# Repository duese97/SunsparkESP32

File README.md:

# SunsparkESP32
A new ESP32 hardware platform for low power applications.

This PCB utilizes a small solar cell in order to harvest energy and store it in a supercapacitor.

*The rendered PCB for the SunsparkESP32*

## Features
1. ESP32 S2 Mini module with a single core MCU: Most projects utilize one core anyway or don't benefit much form a second one. So no current is wasted by idling unnecessary.
2. Native USB support: Converter for RS232 can be connected externally. Many USB to RS232 transceivers have a high quiescent consumption. They are mostly needed for debugging, in order to show data to a console. Flashing the chip also works via the USB bootloader (and is also faster).
3. Integrated open drain MOSFET: Control high power external peripherals and turn them off when not needed.
4. VBUS from USB utilized automatically as backup supply, so debugging does not drain the supercap.
5. Optional RF95/96/97/98 LoRa module can be added (library used: https://github.com/sandeepmistry/arduino-LoRa/tree/master)

## Application example
I included some FW which realizes a simple WiFI weather station with a common BME280. However it can be easily altered to work with different or more sensors as well. It works well enough that it can sustain it's 10min scheduled data delivery indoors, in my living room.

Shutting down/entering deepsleep immediately after sending the UDP packet seems not to work (underlying RTOS or network stack takes some time). Thus I additionally set up the the UDP Server in a way that it sends a small sting back, upon receiving data.
The provided code does not utilizes this any further, but it could be a nice way for a two way communication. The ESP32 will run 1s at most, an then enter sleep again:

*Example flow for parsing incoming results in Node RED*

There is also some small logic, which handles a depletion (or charging) of the supercap by altering the deepsleep period.

I found it helpful to include a runtime checked "debug mode". Tieing a GPIO to high, and to "artificially" shorten the sleep time, so I can debug more easily. Setting it to low put it back into "normal" mode and also disabled some UART prints.

Note: Altered Adafruit_BME280::begin so that is does NOT call
Adafruit_BME280::init upon each wakeup of device -> sensor is permanently
supplied with VCC and does not need a lengthy re-init each time

## Requirements for external components/assembly
1. The open circuit voltage of the solar cell should not exceed 3.3V. Recommended is 1.5V @ 0.65W
2. Make sure to protect the PCB when using it outdoors. Especially the Mega Ohm resistors are sensitive to water. I use clear nail polish for this. 
*The PCB with the solar cell and a BME280 soldered to it. The 433MHz antenna for the RF96 is also visible.*
3. Mechanically a 3D printed assembly can accommodate the circuit shown above. The solar cell can be glued to the housing. 
*The 3D printed enclosure.*

## Errata
### V3 board
1. Current consumption with LoRa module seems too high in idle (when in deepsleep)
2. Still issues with occasional brownouts, when using WiFi
### V2 board
1. ~~USB VCOM for bootloader not working -> GND from USB and GND1 from ESP differ?~~ Forgot to compile with USB CDC enabled
2. BOOT button only working when Supercap is sufficiently charged?
3. Linear 3V3 regulator instantly produced some magic smoke upon connecting VBUS from USB :) There seem to be different pinouts for the same footprint of the same IC!
4. VREF for ADP5090 is too low and not constant

## Charging estimation
### V2 board
In direct sunlight: ~40mA, in the shade with average cloudiness: 2mA.

## Current consumption estimation
General testing consists of the board being flashed with a WiFi UDP client. It posts ~50B of data every 10 minutes to a Node RED UDP server. Static IP config is utilized, to avoid waiting for the DHCP.
Active time is about 0.5s, while sleeping the rest of the time.
The challenge are the short current bursts when the WiFi peripheral is actively used:

*Scoped voltage over a shunt during board activity*

Values for estimating discharging of capacitor:
### V2 board
Active: 45mA; Sleep: 10µA; 50µA average

Improvements mostly due to better ceramic caps (?)
### V1 board
Active: 30mA; Sleep: 90µA; 115µA average

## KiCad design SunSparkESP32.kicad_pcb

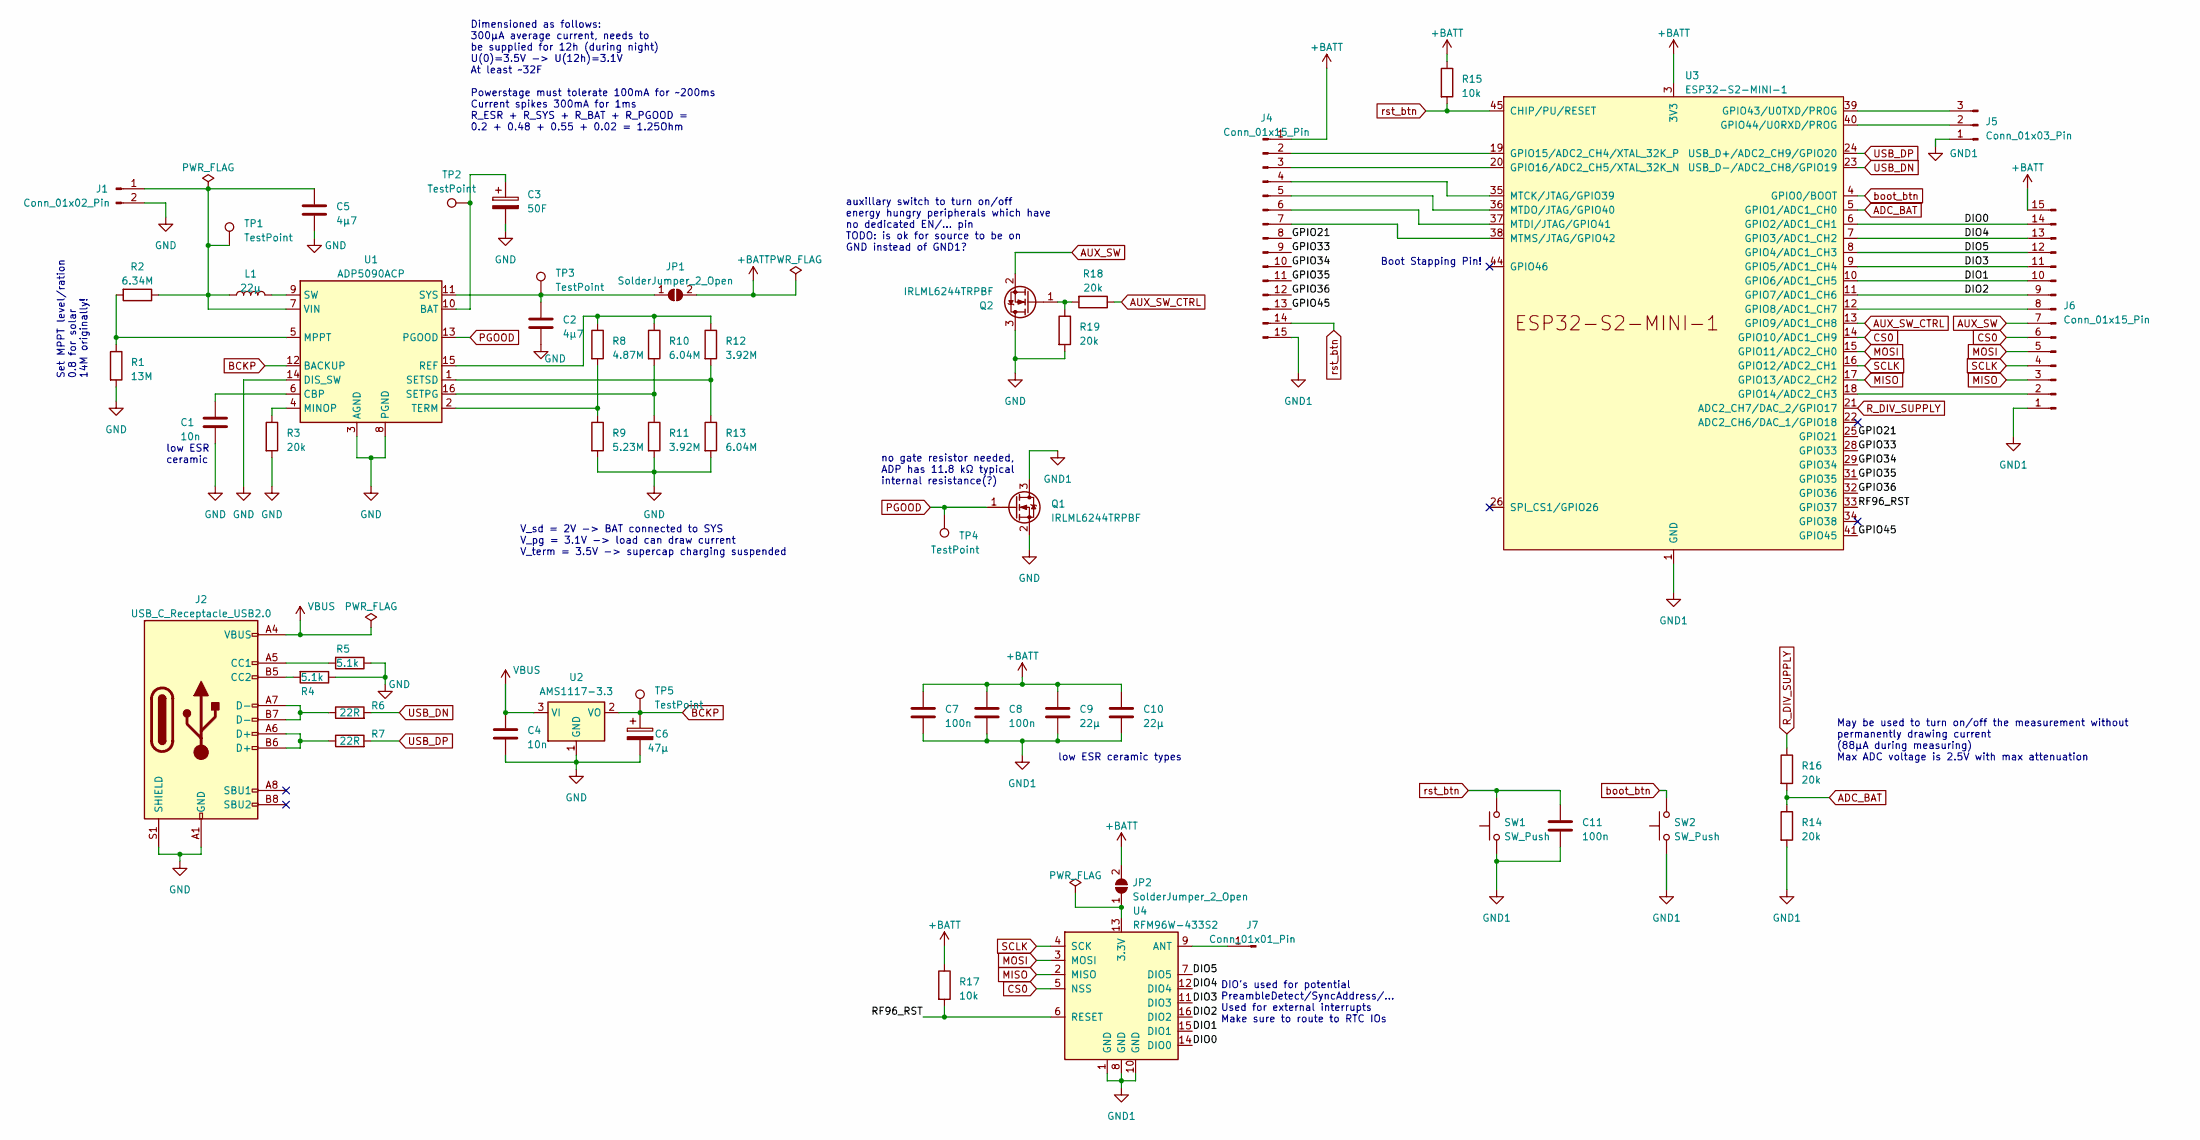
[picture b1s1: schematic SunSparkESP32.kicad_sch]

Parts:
C1, C4: 10n; C_0805_2012Metric_Pad1.18x1.45mm_HandSolder
C2, C5: 4µ7; C_0805_2012Metric_Pad1.18x1.45mm_HandSolder
C3: 50F; CP_Radial_D10.0mm_P5.00mm
C6: 47µ; CP_Elec_5x3
C7, C8, C11: 100n; C_0805_2012Metric_Pad1.18x1.45mm_HandSolder
C9, C10: 22µ; C_1206_3216Metric
J1: Conn_01x02_Pin; PinSocket_1x02_P2.54mm_Vertical
J2: USB_C_Receptacle_USB2.0; USB_C_Receptacle_GCT_USB4105-xx-A_16P_TopMnt_Horizontal
J4, J6: Conn_01x15_Pin; PinSocket_1x15_P2.54mm_Vertical
J5: Conn_01x03_Pin; PinSocket_1x03_P2.54mm_Vertical
J7: Conn_01x01_Pin; TestPoint_THTPad_D1.5mm_Drill0.7mm
JP1, JP2: SolderJumper_2_Open; SolderJumper-2_P1.3mm_Open_RoundedPad1.0x1.5mm
L1: 22µ; L_Coilcraft_LPS4018
Q1, Q2: IRLML6244TRPBF; SOT-23
R1: 13M; R_0805_2012Metric_Pad1.20x1.40mm_HandSolder
R2: 6.34M; R_0805_2012Metric_Pad1.20x1.40mm_HandSolder
R3, R14, R16, R18, R19: 20k; R_0805_2012Metric_Pad1.20x1.40mm_HandSolder
R4, R5: 5.1k; R_0805_2012Metric_Pad1.20x1.40mm_HandSolder
R6, R7: 22R; R_0805_2012Metric_Pad1.20x1.40mm_HandSolder
R8: 4.87M; R_0805_2012Metric_Pad1.20x1.40mm_HandSolder
R9: 5.23M; R_0805_2012Metric_Pad1.20x1.40mm_HandSolder
R10, R13: 6.04M; R_0805_2012Metric_Pad1.20x1.40mm_HandSolder
R11, R12: 3.92M; R_0805_2012Metric_Pad1.20x1.40mm_HandSolder
R15, R17: 10k; R_0805_2012Metric_Pad1.20x1.40mm_HandSolder
SW1, SW2: SW_Push; SW_Tactile_SPST_NO_Straight_CK_PTS636Sx25SMTRLFS
TP1, TP2, TP3, TP4, TP5: TestPoint; TestPoint_Pad_D1.0mm
U1: ADP5090ACP; LFCSP-16-1EP_3x3mm_P0.5mm_EP1.7x1.7mm
U2: AMS1117-3.3; SOT-223-3_TabPin2
U3: ESP32-S2-MINI-1
U4: RFM96W-433S2; HOPERF_RFM9XW_SMD

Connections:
+BATT: C7.1, C8.1, C9.1, C10.1, J4.1, J6.15, JP1.2 (B), JP2.2 (B), R15.1, R17.1, U3.3 (3V3)
/DIO0: J6.14, U3.6 (GPIO2/ADC1_CH1), U4.14 (DIO0)
/DIO1: J6.10, U3.10 (GPIO6/ADC1_CH5), U4.15 (DIO1)
/DIO2: J6.9, U3.11 (GPIO7/ADC1_CH6), U4.16 (DIO2)
/DIO3: J6.11, U3.9 (GPIO5/ADC1_CH4), U4.11 (DIO3)
/DIO4: J6.13, U3.7 (GPIO3/ADC1_CH2), U4.12 (DIO4)
/DIO5: J6.12, U3.8 (GPIO4/ADC1_CH3), U4.7 (DIO5)
/GPIO21: J4.8, U3.25 (GPIO21)
/GPIO33: J4.9, U3.28 (GPIO33)
/GPIO34: J4.10, U3.29 (GPIO34)
/GPIO35: J4.11, U3.31 (GPIO35)
/GPIO36: J4.12, U3.32 (GPIO36)
/GPIO45: J4.13, U3.41 (GPIO45)
/RF96_RST: R17.2, U3.33 (GPIO37), U4.6 (RESET)
ADC_BAT: R14.1, R16.2, U3.5 (GPIO1/ADC1_CH0)
AUX_SW: J6.7, Q2.2 (S)
AUX_SW_CTRL: R18.1, U3.13 (GPIO9/ADC1_CH8)
BCKP: C6.1, TP5.1, U1.12 (BACKUP), U2.2 (VO)
CS0: J6.6, U3.14 (GPIO10/ADC1_CH9), U4.5 (NSS)
GND: C1.2, C2.2, C3.2, C4.2, C5.2, C6.2, J1.2, J2.A1 (GND), J2.A12 (GND), J2.B1 (GND), J2.B12 (GND), J2.S1 (SHIELD), Q1.2 (S), Q2.3 (D), R1.2, R3.2, R4.1, R5.1, R9.2, R11.2, R13.2, R19.2, U1.3 (AGND), U1.8 (PGND), U1.14 (DIS_SW), U1.17 (AGND), U2.1 (GND)
GND1: C7.2, C8.2, C9.2, C10.2, C11.2, J4.15, J5.1, J6.1, Q1.3 (D), R14.2, SW1.1, SW2.1, U3.1 (GND), U3.2 (GND), U3.30 (GND), U3.42 (GND), U3.43 (GND), U3.46 (GND), U3.47 (GND), U3.48 (GND), U3.49 (GND), U3.50 (GND), U3.51 (GND), U3.52 (GND), U3.53 (GND), U3.54 (GND), U3.55 (GND), U3.56 (GND), U3.57 (GND), U3.58 (GND), U3.59 (GND), U3.60 (GND), U3.61 (GND), U3.62 (GND), U3.63 (GND), U3.64 (GND), U3.65 (GND), U4.1 (GND), U4.8 (GND), U4.10 (GND)
MISO: J6.3, U3.17 (GPIO13/ADC2_CH2), U4.2 (MISO)
MOSI: J6.5, U3.15 (GPIO11/ADC2_CH0), U4.3 (MOSI)
unnamed: C5.1, J1.1, L1.1, R2.1, TP1.1, U1.7 (VIN)
unnamed: J2.A5 (CC1), R5.2
unnamed: J2.B5 (CC2), R4.2
unnamed: J2.A6 (D+), J2.B6 (D+), R7.1
unnamed: J2.A7 (D-), J2.B7 (D-), R6.1
unnamed: J4.2, U3.19 (GPIO15/ADC2_CH4/XTAL_32K_P)
unnamed: J4.3, U3.20 (GPIO16/ADC2_CH5/XTAL_32K_N)
unnamed: J4.4, U3.35 (MTCK/JTAG/GPIO39)
unnamed: J4.5, U3.36 (MTDO/JTAG/GPIO40)
unnamed: J4.6, U3.37 (MTDI/JTAG/GPIO41)
unnamed: J4.7, U3.38 (MTMS/JTAG/GPIO42)
unnamed: J5.2, U3.40 (GPIO44/U0RXD/PROG)
unnamed: J5.3, U3.39 (GPIO43/U0TXD/PROG)
unnamed: J6.2, U3.18 (GPIO14/ADC2_CH3)
unnamed: J6.8, U3.12 (GPIO8/ADC1_CH7)
unnamed: J7.1, U4.9 (ANT)
unnamed: C2.1, JP1.1 (A), TP3.1, U1.11 (SYS)
unnamed: JP2.1 (A), U4.13 (3.3V)
unnamed: Q2.1 (G), R18.2, R19.1
unnamed: C3.1, TP2.1, U1.10 (BAT)
unnamed: C1.1, U1.6 (CBP)
unnamed: R3.1, U1.4 (MINOP)
unnamed: R1.1, R2.2, U1.5 (MPPT)
unnamed: R8.1, R10.1, R12.1, U1.15 (REF)
unnamed: R10.2, R11.1, U1.16 (SETPG)
unnamed: R12.2, R13.1, U1.1 (SETSD)
unnamed: L1.2, U1.9 (SW)
unnamed: R8.2, R9.1, U1.2 (TERM)
PGOOD: Q1.1 (G), TP4.1, U1.13 (PGOOD)
R_DIV_SUPPLY: R16.1, U3.21 (ADC2_CH7/DAC_2/GPIO17)
SCLK: J6.4, U3.16 (GPIO12/ADC2_CH1), U4.4 (SCK)
USB_DN: R6.2, U3.23 (USB_D-/ADC2_CH8/GPIO19)
USB_DP: R7.2, U3.24 (USB_D+/ADC2_CH9/GPIO20)
VBUS: C4.1, J2.A4 (VBUS), J2.A9 (VBUS), J2.B4 (VBUS), J2.B9 (VBUS), U2.3 (VI)
boot_btn: SW2.2, U3.4 (GPIO0/BOOT)
rst_btn: C11.1, J4.14, R15.2, SW1.2, U3.45 (CHIP/PU/RESET)

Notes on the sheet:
Set MPPT level/ration 0.8 for solar 14M originally!
no gate resistor needed, ADP has 11.8 kΩ typical internal resistance(?)
low ESR ceramic types
Dimensioned as follows: 300µA average current, needs to be supplied for 12h (during night) U(0)=3.5V -> U(12h)=3.1V At least ~32F Powerstage must tolerate 100mA for ~200ms Current spikes 300mA for 1ms R_ESR + R_SYS + R_BAT + R_PGOOD = 0.2 + 0.48 + 0.55 + 0.02 = 1.25Ohm
low ESR ceramic
May be used to turn on/off the measurement without permanently drawing current (88µA during measuring) Max ADC voltage is 2.5V with max attenuation
V_sd = 2V -> BAT connected to SYS V_pg = 3.1V -> load can draw current V_term = 3.5V -> supercap charging suspended
auxillary switch to turn on/off energy hungry peripherals which have no dedicated EN/... pin TODO: is ok for source to be on GND instead of GND1?
DIO's used for potential PreambleDetect/SyncAddress/... Used for external interrupts Make sure to route to RTC IOs
Boot Stapping Pin!

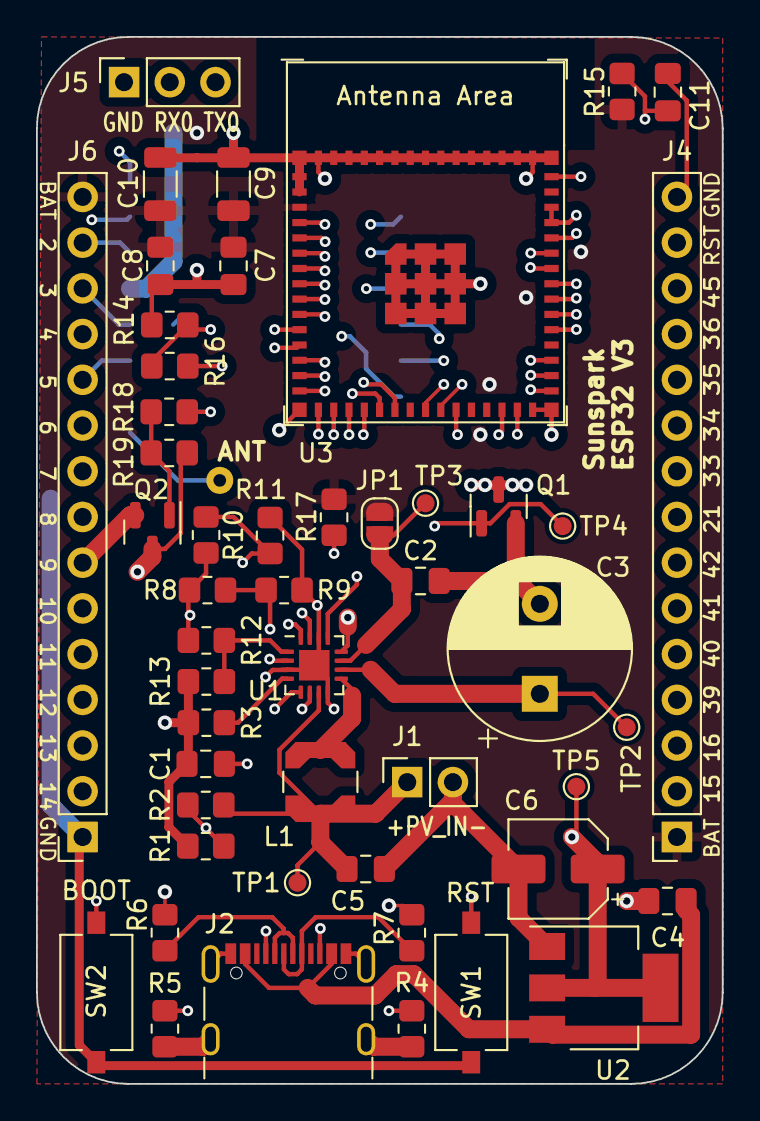
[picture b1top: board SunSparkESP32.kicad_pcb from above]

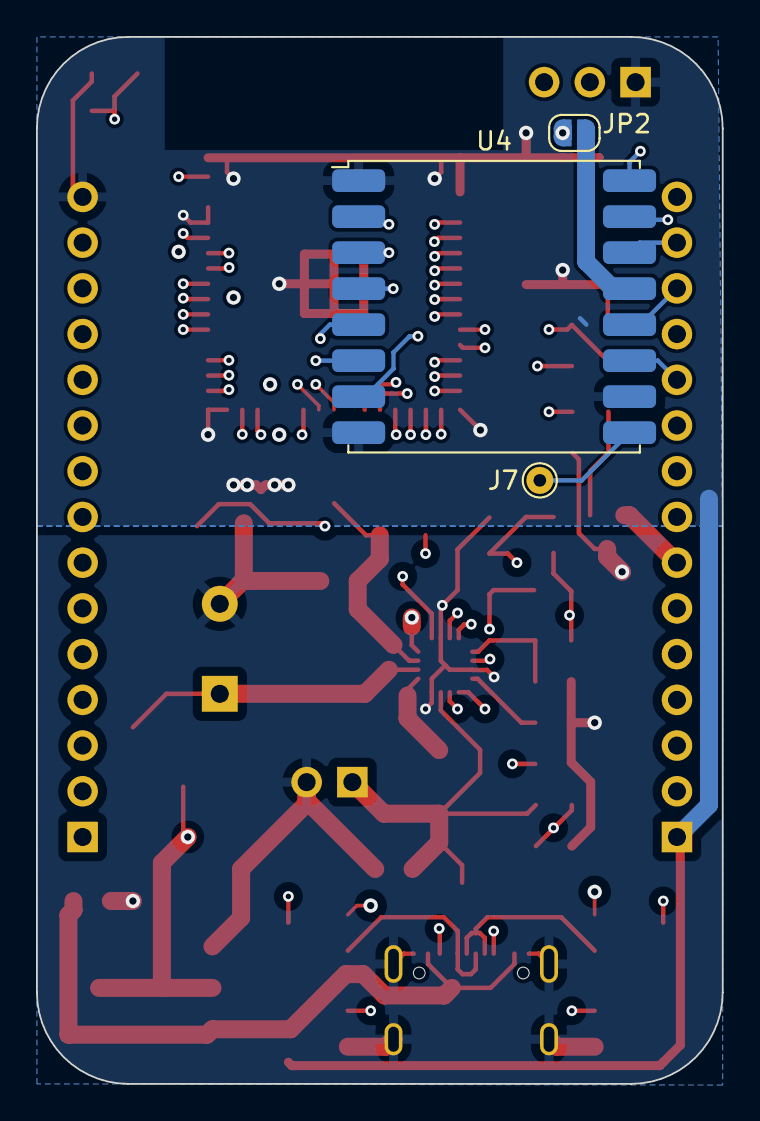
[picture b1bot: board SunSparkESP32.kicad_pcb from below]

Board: 4 copper layers, 38.1 x 58.2 mm, 52 parts (3 on the bottom side), 59 nets.

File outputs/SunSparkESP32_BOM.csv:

Id,Designator,Footprint,Quantity,Designation,Manufacturer,Comment,Mouser #
1,"C5,C2",C_0805_2012Metric_Pad1.18x1.45mm_HandSolder,2,4µ7,C2012X5R1C475M085AB,"low ESR, Generic 0805",810-C2012X5R1C475M0B
2,L1,L_Coilcraft_LPS4018,1,22µ,LPS4018-223MRC,,994-LPS4018-223MRC 
3,U1,LFCSP-16-1EP_3x3mm_P0.5mm_EP1.7x1.7mm,1,ADP5090ACP,ADP5090ACPZ-2-R7,,584-ADP5090ACPZ-2-R7 
4,"R18,R19,R3,R14,R16",R_0805_2012Metric_Pad1.20x1.40mm_HandSolder,5,20k,,Generic 0805,
5,"C4,C1",C_0805_2012Metric_Pad1.18x1.45mm_HandSolder,2,10n,C0805X103K2RAC3316 ,low ESR and leakage type,80-C0805X103K2R3316 
6,"R6,R7",R_0805_2012Metric_Pad1.20x1.40mm_HandSolder,2,22R,,Generic 0805,
7,"R12,R11",R_0805_2012Metric_Pad1.20x1.40mm_HandSolder,2,3.92M,,Generic 0805,
8,C6,CP_Elec_5x3,1,47µ,865080242004,,710-865080242004 
9,"TP5,TP3,TP4,TP2,TP1",TestPoint_Pad_D1.0mm,5,TestPoint,,,
10,R9,R_0805_2012Metric_Pad1.20x1.40mm_HandSolder,1,5.23M,,Generic 0805,
11,"C8,C11,C7",C_0805_2012Metric_Pad1.18x1.45mm_HandSolder,3,100n,,Generic 0805,
12,R8,R_0805_2012Metric_Pad1.20x1.40mm_HandSolder,1,4.87M,,Generic 0805,
13,U3,ESP32-S2-MINI-1,1,ESP32-S2-MINI-1,ESP32-S2-MINI-1-N4,,356-ESP32-S2-MINI-1 
14,"SW2,SW1",SW_Tactile_SPST_NO_Straight_CK_PTS636Sx25SMTRLFS,2,SW_Push,PTS636 SM25J SMTR LFS,,611-PTS636SM25JSMTRL 
15,R15,R_0805_2012Metric_Pad1.20x1.40mm_HandSolder,1,10k,,Generic 0805,
16,J2,USB_C_Receptacle_GCT_USB4105-xx-A_16P_TopMnt_Horizontal,1,USB_C_Receptacle_USB2.0,USB4105-GF-A ,,640-USB4105-GF-A 
17,J5,PinSocket_1x03_P2.54mm_Vertical,1,Conn_01x03_Pin,,generic pin header,
18,"R5,R4",R_0805_2012Metric_Pad1.20x1.40mm_HandSolder,2,5.1k,,Generic 0805,
19,"Q1,Q2",SOT-23,2,IRLML6244TRPBF,IRLML6244TRPBF,,942-IRLML6244TRPBF 
20,"C9,C10",C_1206_3216Metric,2,22µ,C3216JB1C226M160AB,low ESR,810-C3216JB1C226M16B 
21,"JP1,JP2",SolderJumper-2_P1.3mm_Open_RoundedPad1.0x1.5mm,2,SolderJumper_2_Open,,,
22,R1,R_0805_2012Metric_Pad1.20x1.40mm_HandSolder,1,13M,,Generic 0805,
23,J1,PinSocket_1x02_P2.54mm_Vertical,1,Conn_01x02_Pin,,generic pin header,
24,"R10,R13",R_0805_2012Metric_Pad1.20x1.40mm_HandSolder,2,6.04M,,Generic 0805,
25,"J4,J6",PinSocket_1x15_P2.54mm_Vertical,2,Conn_01x15_Pin,,generic pin header,
26,U2,SOT-223-3_TabPin2,1,AMS1117-3.3,TLV1117LV33DCYT ,"Watch for variants with different pinning, not any generic 1117 will work!!!", 595-TLV1117LV33DCYT 
27,C3,CP_Radial_D10.0mm_P5.00mm,1,50F,VMF506M3R8 ,"Must tolerate 3.6V, 30..50F is ok",598-VMF506M3R8 
28,R2,R_0805_2012Metric_Pad1.20x1.40mm_HandSolder,1,6.34M,,Generic 0805,
29,J7,TestPoint_THTPad_D1.5mm_Drill0.7mm,1,Conn_01x01_Pin,,generic pin header,
30,U4,HOPERF_RFM9XW_SMD,1,RFM96W-433S2,,,

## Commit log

2023-05-17 Added basic project files
2023-05-19 Reworked placement of components Added low side switch instead of complicated high side IC Enhanced readme
2023-05-20 Minor enhancements to PCB Added BOM and PDF output
2023-05-22 Added optional footprint for RF95/96/97/98 footprint
2023-05-24 Rework due to first review -Replaced electrolytic caps with low ESR ceramic ones -Routing optimizations Also added possible connection for backup battery Routed some DIOs from LoRa module on controll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
2023-05-27 Finalized last review points, enhanced doc -Added Diode to prevent discharge from supercap into LDO -Updated BOM -Made readme nicer
2023-05-27 Last preparations for V2 board -Generated gerber + drill files for production -Updated PDF schematic output
2023-05-27 Added Routing for DIO pins of modem
2023-05-28 place hole to pass checks
2023-05-28 Updated fabrication + schematic output due to additional DIO routing
2023-05-28 Removed some ERC warnings -Added NC flag to non connected pins Remapped some DIOs to actual RTC GPIOs, so that external interrupts in deep sleep are possible
2023-06-17 Various fixes due to V2 testing -GPIO46 now not routed to external pin header -Corrected some silk -Cleaned up schematic
2023-06-27 Removed some debugging connectors -Directly connected backup supply -Removed series connector to supercap
2023-07-03 Minor improvements on documentation
2023-07-15 Final adjustments for release preparation -Updated schematics, BOM and fabrication files -Added solder jumper so RFM96 can be powered independently
2023-07-16 Added SW template for utilization as wifi sensor node
    Enhanced documentation, cleaned up
    Provided code for BME280, but can also be used with other sensors
    Note: Altered Adafruit_BME280::begin so that is does NOT call
    Adafruit_BME280::init upon each wakeup of device -> sensor is permanently
    supplied with VCC and does not need a lengthy re-init each time
2023-07-29 Demo SW improvements
2023-09-26 Fixed new pinning, added pulldown for debug option
2023-09-29 connected RF96 pin to µC instead of reset button
2023-10-01 Added compile switch for using wifi or RF96 module
2023-10-11 Added housing and updated documentation
